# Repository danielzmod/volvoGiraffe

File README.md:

# volvoGiraffe
Eagle schematic and pcb of giraffe for Volvo V40.

Dependencies of parts library:
lib/*.lbr <br>
https://github.com/sparkfun/SparkFun-Eagle-Libraries <br>
https://github.com/commaai/neo/tree/master/board/comma.ai.lbr <br>

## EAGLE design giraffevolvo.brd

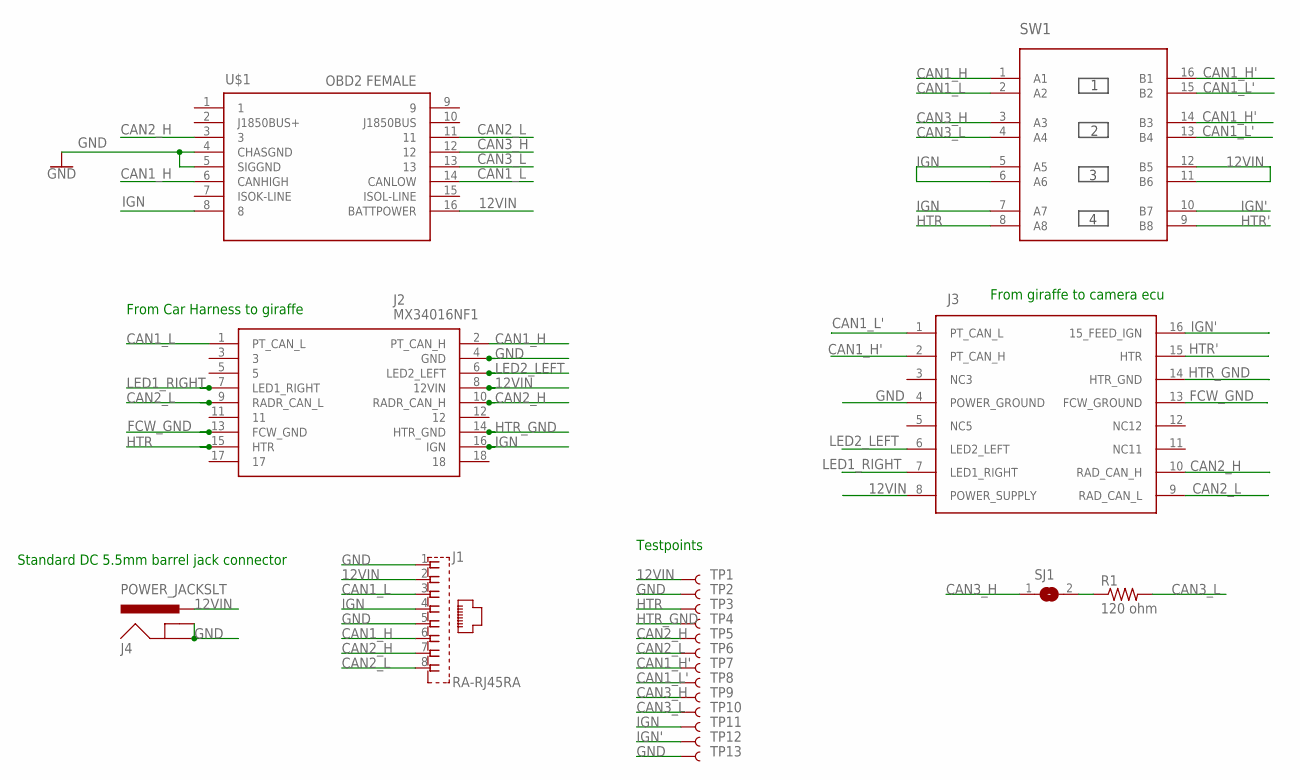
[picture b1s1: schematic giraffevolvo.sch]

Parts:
J1: RA-RJ45RA; RA-RJ45
J2: MX34016NF1
J3: MX34016SF1
J4: POWER_JACKSLT; POWER_JACK_SLOT
R1: 120 ohm; 0603-R
SJ1: SJ
SW1: 4XDPSTSMT; 4-DPST
TP1, TP2, TP3, TP4, TP5, TP6, TP7, TP8, TP9, TP10, TP11, TP12, TP13: TEST-POINT2; PAD.02X.02
U$1: OBDIIFEMALE; OBDII-FEMALE

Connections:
12VIN: J1.2, J2.8 (12VIN), J3.8 (POWER_SUPPLY), J4.PWR, SW1.11 (B6), SW1.12 (B5), TP1.P$1, U$1.16 (BATTPOWER)
CAN1_H: J1.6, J2.2 (PT_CAN_H), SW1.1 (A1), U$1.6 (CANHIGH)
CAN1_H': J3.2 (PT_CAN_H), SW1.14 (B3), SW1.16 (B1), TP7.P$1
CAN1_L: J1.3, J2.1 (PT_CAN_L), SW1.2 (A2), U$1.14 (CANLOW)
CAN1_L': J3.1 (PT_CAN_L), SW1.13 (B4), SW1.15 (B2), TP8.P$1
CAN2_H: J1.7, J2.10 (RADR_CAN_H), J3.10 (RAD_CAN_H), TP5.P$1, U$1.3
CAN2_L: J1.8, J2.9 (RADR_CAN_L), J3.9 (RAD_CAN_L), TP6.P$1, U$1.11
CAN3_H: SJ1.1, SW1.3 (A3), TP9.P$1, U$1.12
CAN3_L: R1.2, SW1.4 (A4), TP10.P$1, U$1.13
FCW_GND: J2.13 (FCW_GND), J3.13 (FCW_GROUND)
GND: J1.1, J1.5, J2.4 (GND), J3.4 (POWER_GROUND), J4.GND@1 (GNDBREAK), J4.GND@2 (GND), TP2.P$1, TP13.P$1, U$1.4 (CHASGND), U$1.5 (SIGGND)
HTR: J2.15 (HTR), SW1.8 (A8), TP3.P$1
HTR': J3.15 (HTR), SW1.9 (B8)
HTR_GND: J2.14 (HTR_GND), J3.14 (HTR_GND), TP4.P$1
IGN: J1.4, J2.16 (IGN), SW1.5 (A5), SW1.6 (A6), SW1.7 (A7), TP11.P$1, U$1.8
IGN': J3.16 (15_FEED_IGN), SW1.10 (B7), TP12.P$1
LED1_RIGHT: J2.7 (LED1_RIGHT), J3.7 (LED1_RIGHT)
LED2_LEFT: J2.6 (LED2_LEFT), J3.6 (LED2_LEFT)
unnamed: R1.1, SJ1.2

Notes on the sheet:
From Car Harness to giraffe
Testpoints
Standard DC 5.5mm barrel jack connector
From giraffe to camera ecu

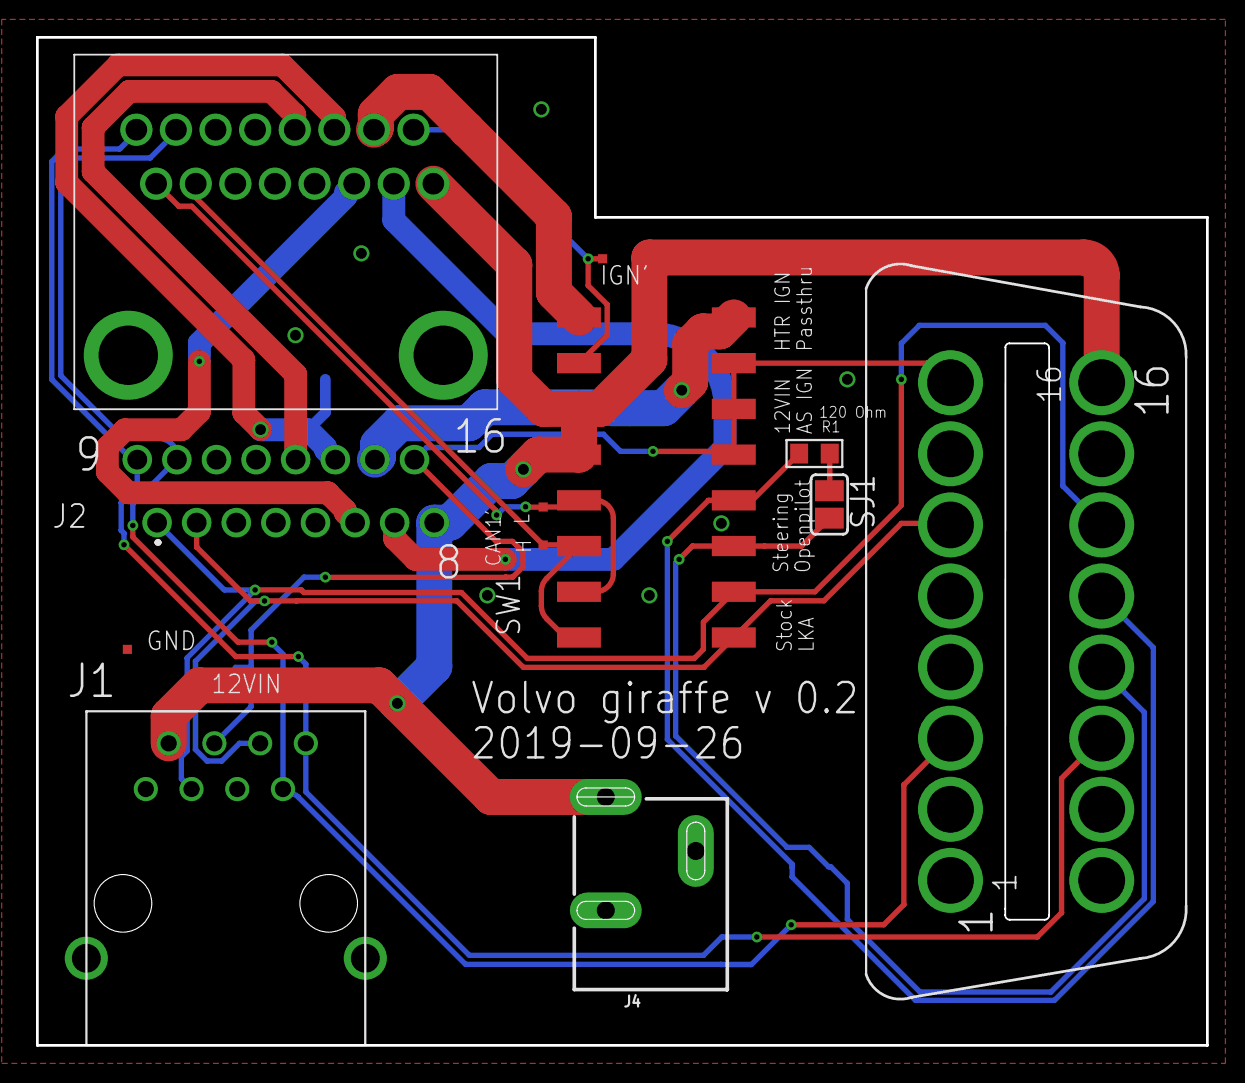
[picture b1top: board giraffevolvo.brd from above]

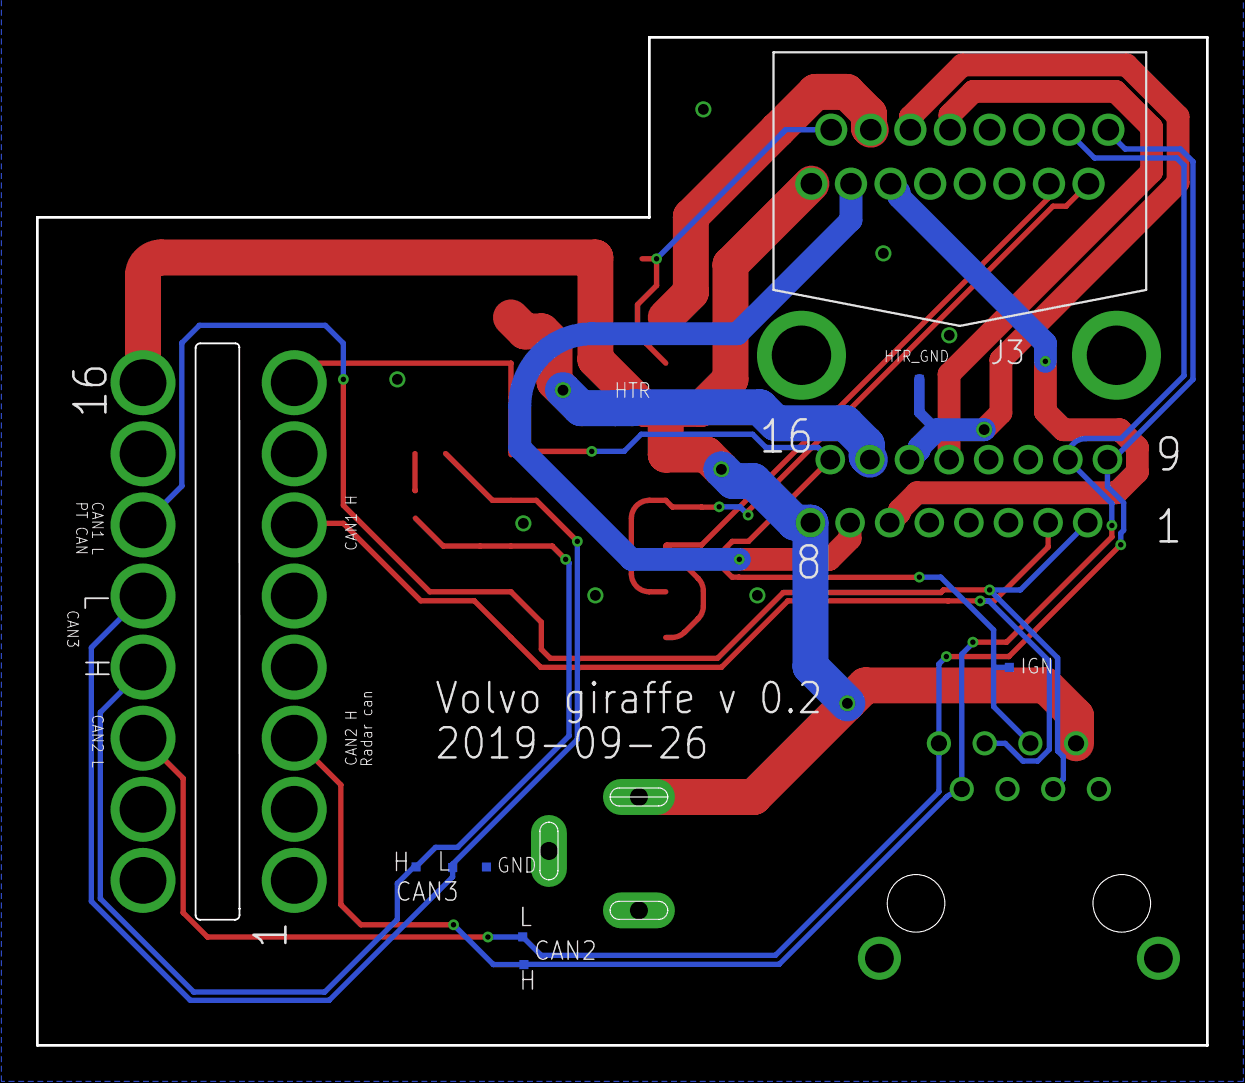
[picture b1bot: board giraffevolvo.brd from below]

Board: 2 copper layers, 65.0 x 56.0 mm, 21 parts (9 on the bottom side), 19 nets.

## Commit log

2020-01-05 Volvo V40 Giraffe

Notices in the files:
parts and their libraries:
SparkFun-Connectors: Licensing: Creative Commons ShareAlike 4.0 International - https://creativecommons.org/licenses/by-sa/4.0
